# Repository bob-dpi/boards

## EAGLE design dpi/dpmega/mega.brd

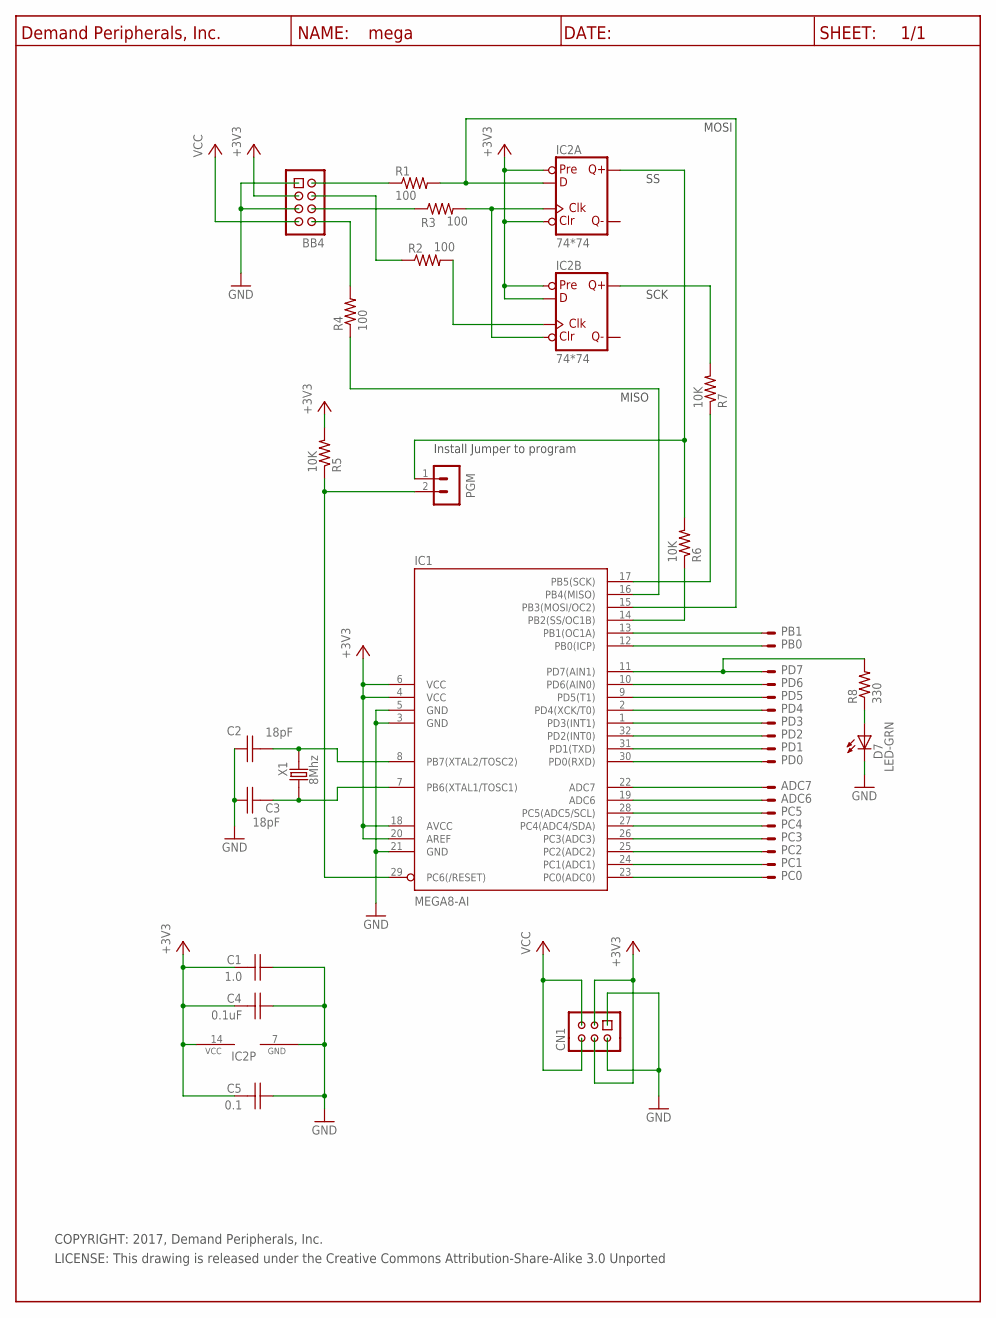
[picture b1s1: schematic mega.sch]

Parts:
ADC6, ADC7: PinHdr254-1(Option); PAD1
BB4: BB4_CON; HDR-4X2
C1: 1.0; C0603
C2, C3: 18pF; C0603
C4: 0.1uF; C0603
C5: 0.1; C0603
CN1: HDR-3X2
D7: LED-GRN; 0805
IC1: MEGA8-AI; TQFP32-08
IC2: 74*74; TSSOP14
PB0, PB1: PinHdr254-1(Option); PAD1
PC0, PC1, PC2, PC3, PC4, PC5: PinHdr254-1(Option); PAD1
PD0, PD1, PD2, PD3, PD4, PD5, PD6, PD7: PinHdr254-1(Option); PAD1
PGM: PinHdr254-2; HDR-2X1
R1, R2, R3, R4: 100; R0603
R5, R6, R7: 10K; R0603
R8: 330; R0603
U$1: DP_FRAME_P; P_FRAME
X1: 8Mhz; NX5032

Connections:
+3V3: BB4.3, C1.2, C4.2, C5.2, CN1.3, CN1.4, IC1.4 (VCC), IC1.6 (VCC), IC1.18 (AVCC), IC1.20 (AREF), IC2.1 (CLR), IC2.4 (PRE), IC2.10 (PRE), IC2.12 (D), IC2.14 (VCC), R5.2
GND: BB4.1, BB4.5, C1.1, C2.1, C3.1, C4.1, C5.1, CN1.1, CN1.2, D7.C, IC1.3 (GND), IC1.5 (GND), IC1.21 (GND), IC2.7 (GND)
unnamed: IC1.29 (PC6(/RESET)), PGM.2 (1), R5.1
unnamed: D7.A, R8.1
unnamed: C3.2, IC1.7 (PB6(XTAL1/TOSC1)), X1.2
unnamed: C2.2, IC1.8 (PB7(XTAL2/TOSC2)), X1.1
unnamed: IC1.23 (PC0(ADC0)), PC0.1
unnamed: IC1.26 (PC3(ADC3)), PC3.1
unnamed: IC1.24 (PC1(ADC1)), PC1.1
unnamed: IC1.25 (PC2(ADC2)), PC2.1
unnamed: IC1.27 (PC4(ADC4/SDA)), PC4.1
unnamed: IC1.28 (PC5(ADC5/SCL)), PC5.1
unnamed: ADC6.1, IC1.19 (ADC6)
unnamed: ADC7.1, IC1.22 (ADC7)
unnamed: IC1.30 (PD0(RXD)), PD0.1
unnamed: IC1.31 (PD1(TXD)), PD1.1
unnamed: IC1.32 (PD2(INT0)), PD2.1
unnamed: IC1.1 (PD3(INT1)), PD3.1
unnamed: IC1.2 (PD4(XCK/T0)), PD4.1
unnamed: IC1.9 (PD5(T1)), PD5.1
unnamed: IC1.10 (PD6(AIN0)), PD6.1
unnamed: IC1.11 (PD7(AIN1)), PD7.1, R8.2
unnamed: IC1.12 (PB0(ICP)), PB0.1
unnamed: IC1.13 (PB1(OC1A)), PB1.1
unnamed: BB4.2, R1.1
unnamed: IC1.15 (PB3(MOSI/OC2)), IC2.2 (D), R1.2
unnamed: BB4.4, R2.1
unnamed: IC2.11 (CLK), R2.2
unnamed: IC2.3 (CLK), IC2.13 (CLR), R3.2
unnamed: BB4.6, R3.1
unnamed: IC2.9 (Q), R7.2
unnamed: IC2.5 (Q), PGM.1 (2), R6.2
unnamed: IC1.16 (PB4(MISO)), R4.1
unnamed: BB4.8, R4.2
unnamed: IC1.14 (PB2(SS/OC1B)), R6.1
unnamed: IC1.17 (PB5(SCK)), R7.1
VCC: BB4.7, CN1.5, CN1.6

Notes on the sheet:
MOSI
MISO
SCK
Install Jumper to program
COPYRIGHT: 2017, Demand Peripherals, Inc.
LICENSE: This drawing is released under the Creative Commons Attribution-Share-Alike 3.0 Unported

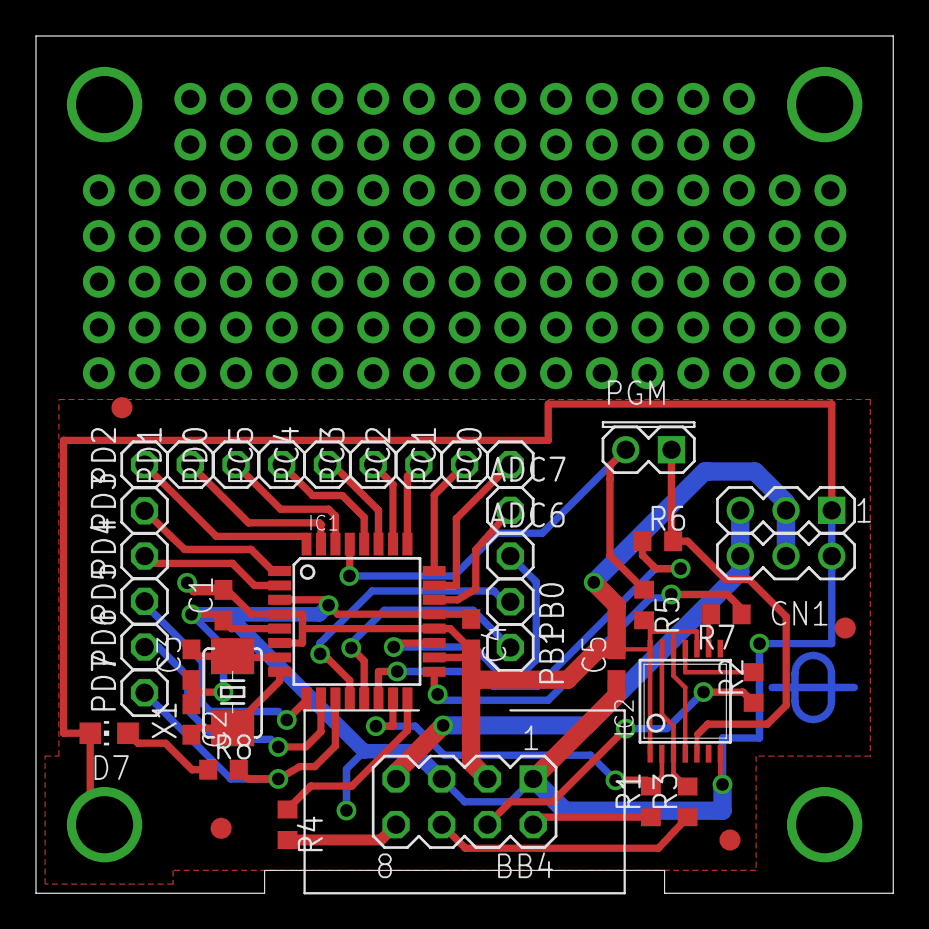
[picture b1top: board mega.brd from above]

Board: 2 copper layers, 47.6 x 47.6 mm, 44 parts (1 on the bottom side), 37 nets.

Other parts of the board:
U$2: DPI-1
U$4, U$5, U$6, U$7: FIDUCIAL

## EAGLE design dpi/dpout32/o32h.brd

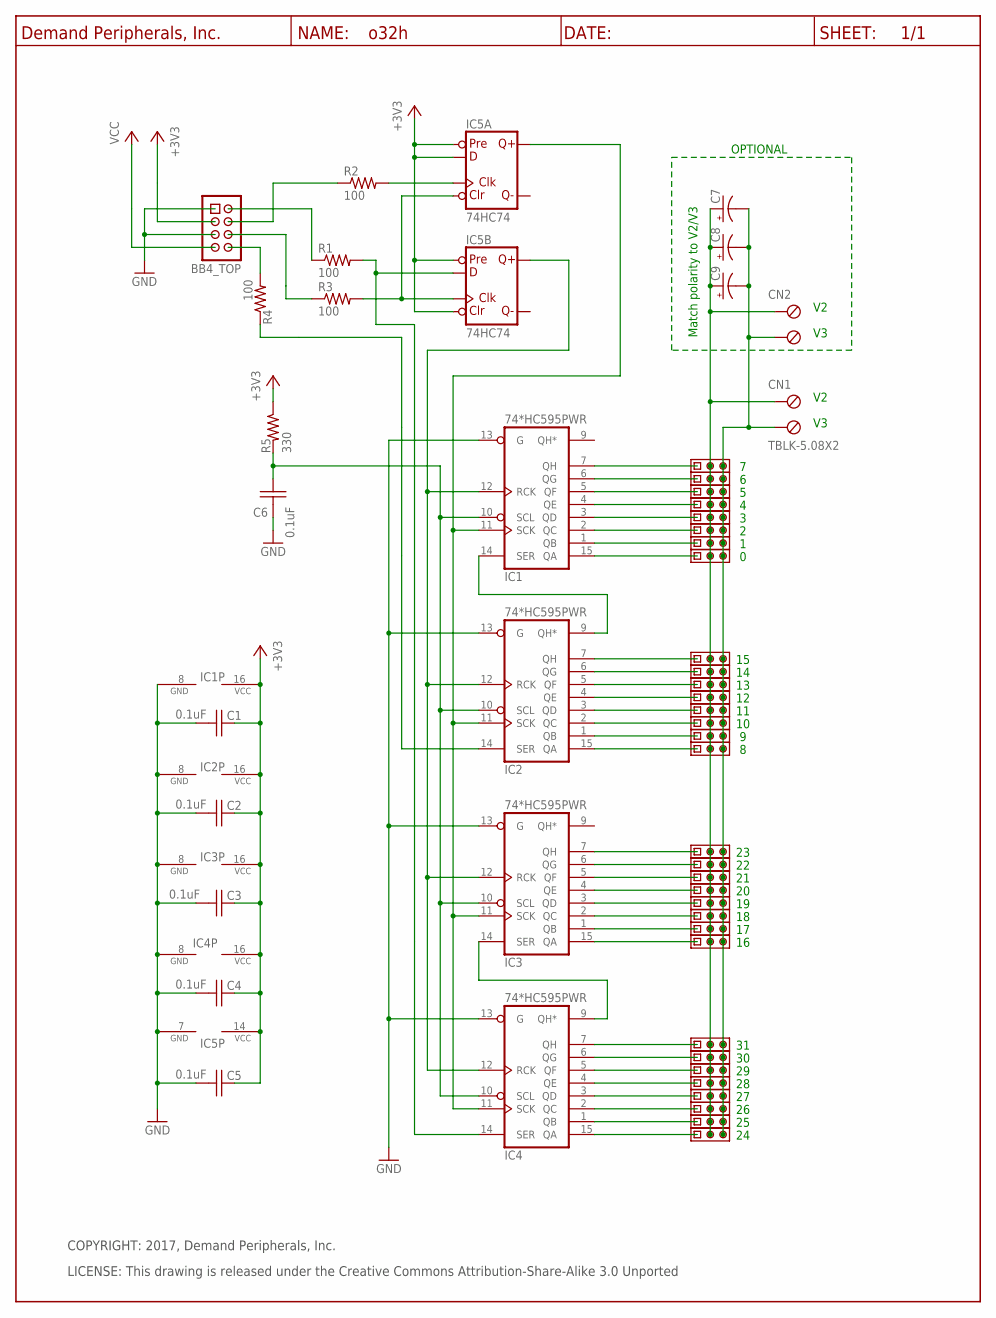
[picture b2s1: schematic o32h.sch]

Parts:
BB4_TOP: Keyed_Pin_Header_4x2(0.1"x0.1"); HDR-4X2
C1, C2, C3, C4, C5, C6: 0.1uF; C0603
C7, C8, C9: OPTIONAL; E7,5-16
CN1, CN2: TBLK-5.08X2; TBLK-5.08-X2
IC1, IC2, IC3, IC4: 74*HC595PWR; SO16
IC5: 74HC74; SO14
R1, R2, R3, R4: 100; R0603
R5: 330; R0603
U$2: DP_FRAME_P; P_FRAME
U$8, U$9, U$10, U$11, U$12, U$13, U$14, U$15, U$16, U$17, U$18, U$19, U$20, U$21, U$22, U$23, U$24, U$25, U$26, U$27, U$28, U$29, U$30, U$31, U$32, U$33, U$34, U$35, U$36, U$37, U$38, U$39: HDR-3X1

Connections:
+3V3: BB4_TOP.3, C1.1, C2.1, C3.1, C4.1, C5.1, IC1.16 (VCC), IC2.16 (VCC), IC3.16 (VCC), IC4.16 (VCC), IC5.2 (D), IC5.4 (PRE), IC5.10 (PRE), IC5.13 (CLR), IC5.14 (VCC), R5.1
GND: BB4_TOP.1, BB4_TOP.5, C1.2, C2.2, C3.2, C4.2, C5.2, C6.2, IC1.8 (GND), IC1.13 (G), IC2.8 (GND), IC2.13 (G), IC3.8 (GND), IC3.13 (G), IC4.8 (GND), IC4.13 (G), IC5.7 (GND)
unnamed: BB4_TOP.8, R4.2
unnamed: IC1.7 (QH), U$8.1
unnamed: IC1.12 (RCK), IC2.12 (RCK), IC3.12 (RCK), IC4.12 (RCK), IC5.9 (Q)
unnamed: IC1.11 (SCK), IC2.11 (SCK), IC3.11 (SCK), IC4.11 (SCK), IC5.5 (Q)
unnamed: IC1.6 (QG), U$9.1
unnamed: IC1.5 (QF), U$10.1
unnamed: IC1.4 (QE), U$11.1
unnamed: IC1.3 (QD), U$12.1
unnamed: IC1.2 (QC), U$13.1
unnamed: IC1.1 (QB), U$14.1
unnamed: IC1.15 (QA), U$15.1
unnamed: IC2.7 (QH), U$16.1
unnamed: IC2.6 (QG), U$17.1
unnamed: IC2.5 (QF), U$18.1
unnamed: IC2.4 (QE), U$19.1
unnamed: IC2.3 (QD), U$20.1
unnamed: IC2.2 (QC), U$21.1
unnamed: IC2.1 (QB), U$22.1
unnamed: IC2.15 (QA), U$23.1
unnamed: IC3.7 (QH), U$24.1
unnamed: IC3.6 (QG), U$25.1
unnamed: IC3.5 (QF), U$26.1
unnamed: IC3.4 (QE), U$27.1
unnamed: IC3.3 (QD), U$28.1
unnamed: IC3.2 (QC), U$29.1
unnamed: BB4_TOP.2, R1.1
unnamed: IC3.1 (QB), U$30.1
unnamed: IC5.3 (CLK), R2.2
unnamed: IC4.14 (SER), IC5.12 (D), R1.2
unnamed: IC5.1 (CLR), IC5.11 (CLK), R3.2
unnamed: IC2.14 (SER), R4.1
unnamed: BB4_TOP.6, R3.1
unnamed: IC3.14 (SER), IC4.9 (QH*)
unnamed: BB4_TOP.4, R2.1
unnamed: IC3.15 (QA), U$31.1
unnamed: C6.1, IC1.10 (SCL), IC2.10 (SCL), IC3.10 (SCL), IC4.10 (SCL), R5.2
unnamed: IC4.7 (QH), U$32.1
unnamed: IC4.6 (QG), U$33.1
unnamed: IC4.5 (QF), U$34.1
unnamed: IC4.4 (QE), U$35.1
unnamed: IC4.3 (QD), U$36.1
unnamed: IC4.2 (QC), U$37.1
unnamed: IC4.1 (QB), U$38.1
unnamed: IC4.15 (QA), U$39.1
unnamed: IC1.14 (SER), IC2.9 (QH*)
V2: C7.+, C8.+, C9.+, CN1.1 (KL), CN2.1 (KL), U$8.2, U$9.2, U$10.2, U$11.2, U$12.2, U$13.2, U$14.2, U$15.2, U$16.2, U$17.2, U$18.2, U$19.2, U$20.2, U$21.2, U$22.2, U$23.2, U$24.2, U$25.2, U$26.2, U$27.2, U$28.2, U$29.2, U$30.2, U$31.2, U$32.2, U$33.2, U$34.2, U$35.2, U$36.2, U$37.2, U$38.2, U$39.2
V3: C7.-, C8.-, C9.-, CN1.2 (KL1), CN2.2 (KL1), U$8.3, U$9.3, U$10.3, U$11.3, U$12.3, U$13.3, U$14.3, U$15.3, U$16.3, U$17.3, U$18.3, U$19.3, U$20.3, U$21.3, U$22.3, U$23.3, U$24.3, U$25.3, U$26.3, U$27.3, U$28.3, U$29.3, U$30.3, U$31.3, U$32.3, U$33.3, U$34.3, U$35.3, U$36.3, U$37.3, U$38.3, U$39.3
VCC: BB4_TOP.7

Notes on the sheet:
COPYRIGHT: 2017, Demand Peripherals, Inc.
LICENSE: This drawing is released under the Creative Commons Attribution-Share-Alike 3.0 Unported
OPTIONAL
Match polarity to V2/V3

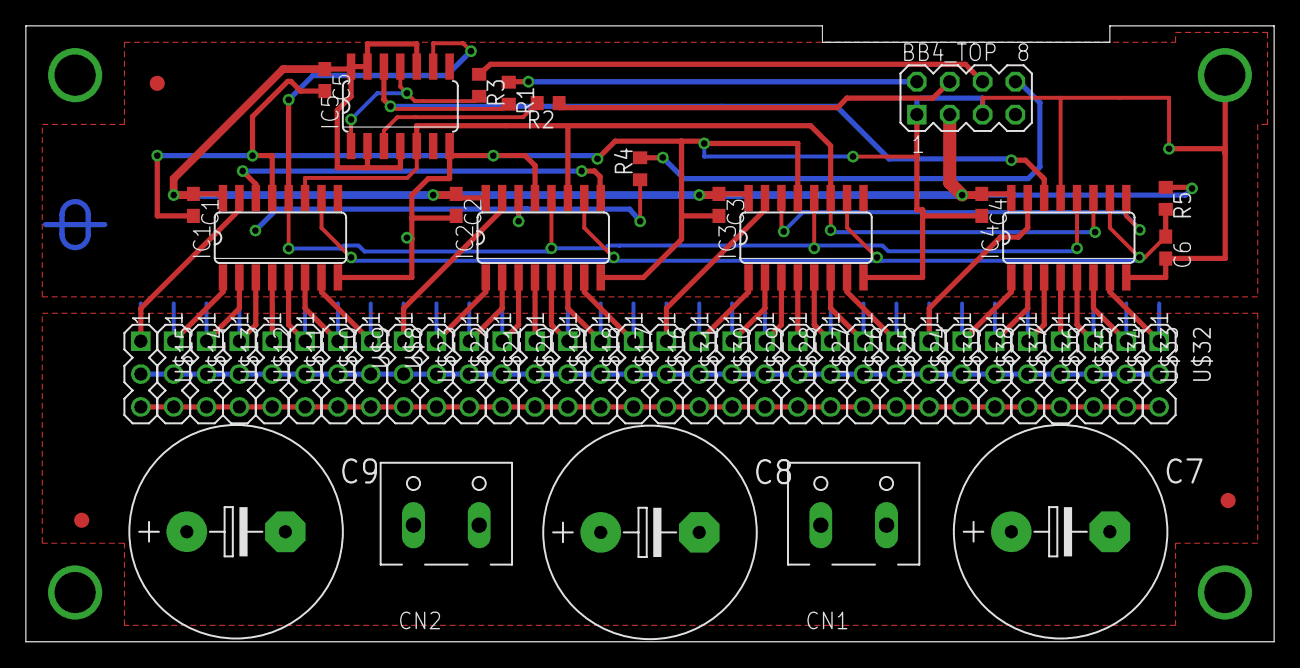
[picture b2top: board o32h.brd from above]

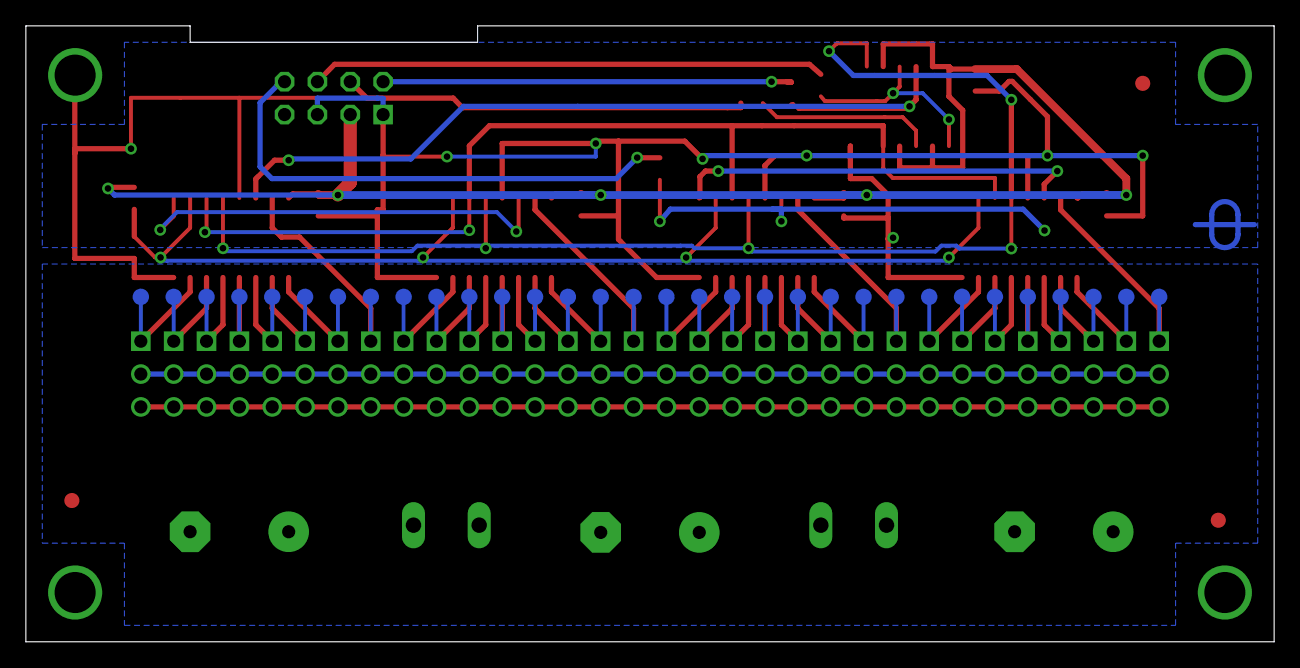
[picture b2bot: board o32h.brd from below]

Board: 2 copper layers, 96.5 x 47.6 mm, 93 parts (33 on the bottom side), 49 nets.

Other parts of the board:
E$1, E$2, E$3, E$4, E$5, E$7, E$8, E$9, E$10, E$11, E$12, E$13, E$14, E$15, E$16, E$17, E$18, E$19, E$20, E$21, E$22, E$23, E$24, E$26, E$27, E$28, E$29, E$30, E$31, E$32, E$33, E$34: TEST-POINT
E$25: P_FRAME
U$1: P_FRAME
U$4, U$5, U$6: FIDUCIAL
U$7: DPI-1

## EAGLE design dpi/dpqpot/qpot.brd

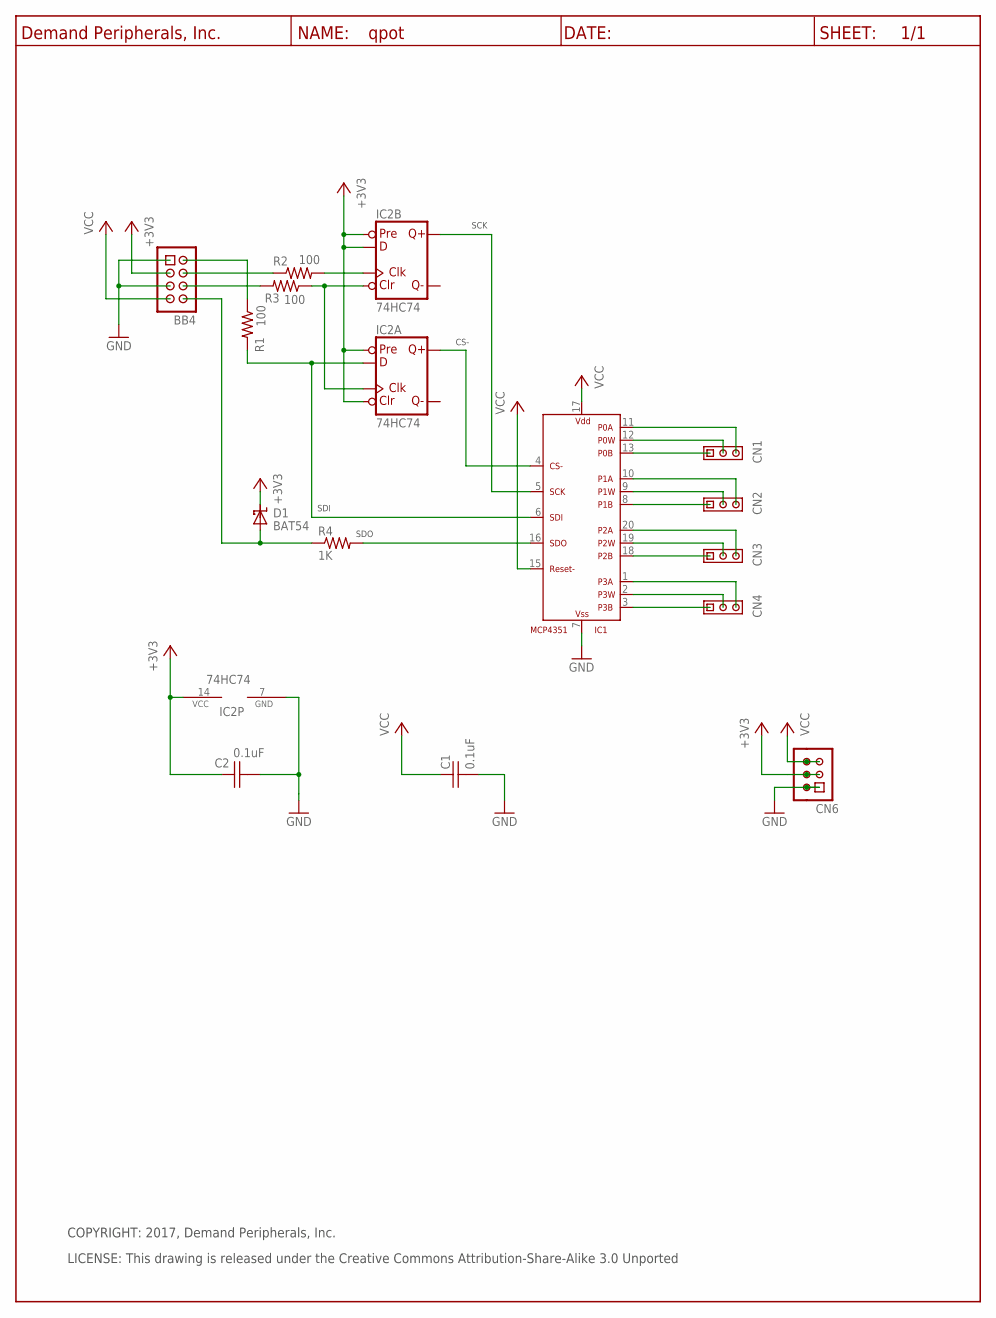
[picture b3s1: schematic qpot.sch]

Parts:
BB4: BB_CON; HDR-4X2
C1, C2: 0.1uF; C0603
CN1, CN2, CN3, CN4: HDR-3X1
CN6: HDR-3X2
D1: BAT54; SOT23
IC1: MCP4351; TSSOP20
IC2: 74HC74; SO14
R1, R2, R3: 100; R0603
R4: 1K; R0603
U$3: DP_FRAME_P; P_FRAME

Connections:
+3V3: BB4.3, C2.1, CN6.3, CN6.4, D1.3 (CC), IC2.1 (CLR), IC2.4 (PRE), IC2.10 (PRE), IC2.12 (D), IC2.14 (VCC)
GND: BB4.1, BB4.5, C1.2, C2.2, CN6.1, CN6.2, IC1.7 (VSS), IC2.7 (GND)
unnamed: CN1.1, IC1.13 (P0B)
unnamed: CN1.2, IC1.12 (P0W)
unnamed: CN1.3, IC1.11 (P0A)
unnamed: CN2.1, IC1.8 (P1B)
unnamed: CN2.2, IC1.9 (P1W)
unnamed: CN2.3, IC1.10 (P1A)
unnamed: BB4.8, D1.1 (A), R4.1
unnamed: IC1.16 (SDO), R4.2
unnamed: IC2.3 (CLK), IC2.13 (CLR), R3.1
unnamed: BB4.4, R2.1
unnamed: IC1.6 (SDI), IC2.2 (D), R1.2
unnamed: IC2.11 (CLK), R2.2
unnamed: CN3.1, IC1.18 (P2B)
unnamed: CN3.2, IC1.19 (P2W)
unnamed: BB4.6, R3.2
unnamed: BB4.2, R1.1
unnamed: CN3.3, IC1.20 (P2A)
unnamed: CN4.1, IC1.3 (P3B)
unnamed: IC1.4 (CS-), IC2.5 (Q)
unnamed: IC1.5 (SCK), IC2.9 (Q)
unnamed: CN4.2, IC1.2 (P3W)
unnamed: CN4.3, IC1.1 (P3A)
VCC: BB4.7, C1.1, CN6.5, CN6.6, IC1.15 (RESET-), IC1.17 (VDD)

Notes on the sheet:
SCK
CS-
SDI
LICENSE: This drawing is released under the Creative Commons Attribution-Share-Alike 3.0 Unported
COPYRIGHT: 2017, Demand Peripherals, Inc.
SDO

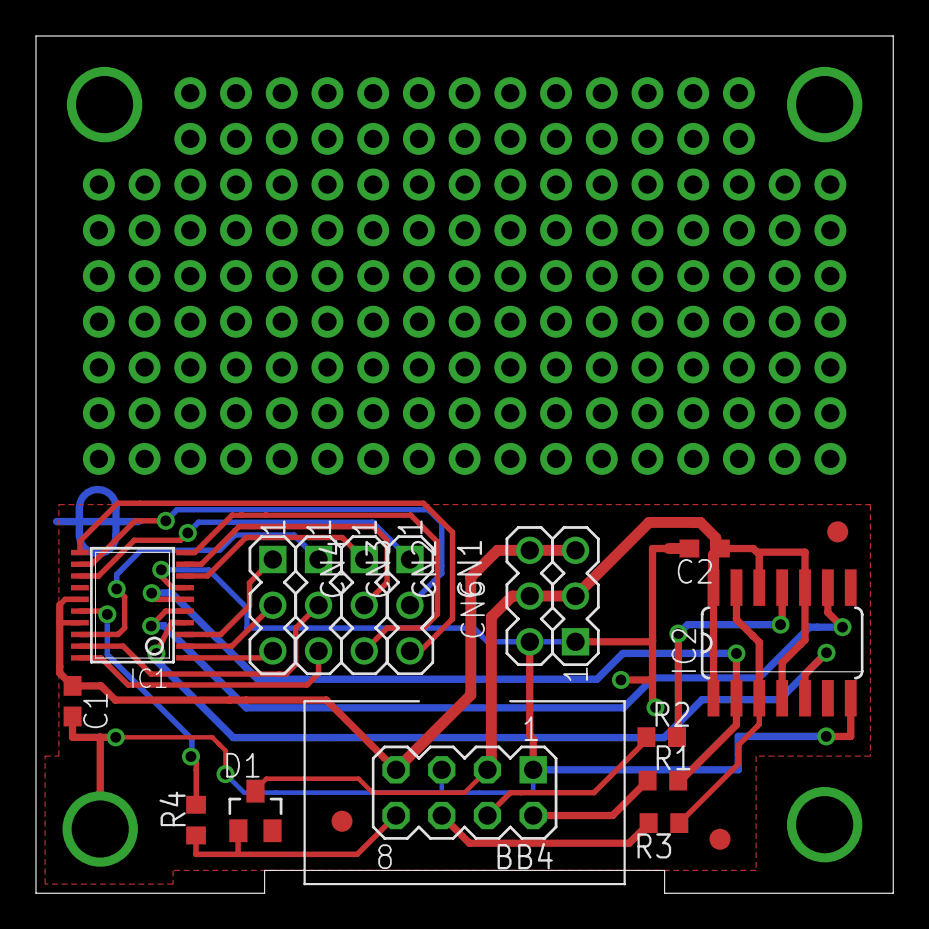
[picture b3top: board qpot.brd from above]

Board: 2 copper layers, 47.6 x 47.6 mm, 20 parts (1 on the bottom side), 25 nets.

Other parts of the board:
U$1: DPI-1
U$4, U$5, U$6: FIDUCIAL

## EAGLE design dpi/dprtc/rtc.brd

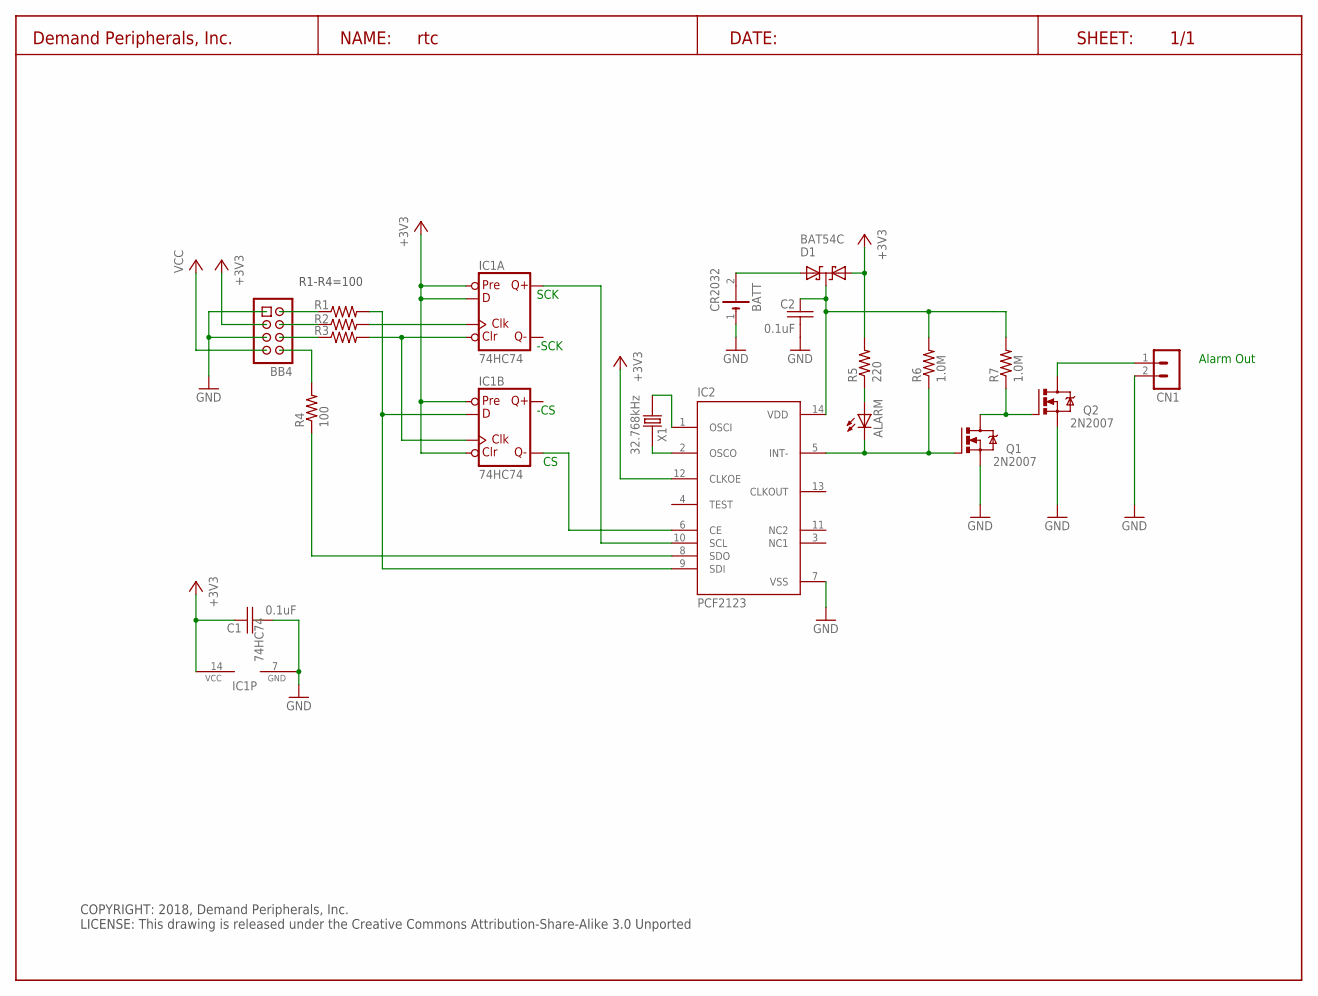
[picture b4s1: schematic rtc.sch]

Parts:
ALARM: Red_LED; 0805
BATT: CR2032; CR2032_KEYSTONE
BB4: BB_CON; HDR-4X2
C1, C2: 0.1uF; C0603
CN1: HDR-2X1-LCK; HDR-2X1
D1: BAT54C; SOT23
IC1: 74HC74; SO14
IC2: PCF2123; TSSOP14
Q1, Q2: 2N2007; SOT23
R1, R2, R3, R4: 100; R0603
R5: 220; R0603
R6, R7: 1.0M; R0603
U$1: DP_FRAME_L; LETTER_L
X1: 32.768kHz; 4-SOJ

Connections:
+3V3: BB4.3, C1.1, D1.2 (A), IC1.2 (D), IC1.4 (PRE), IC1.10 (PRE), IC1.13 (CLR), IC1.14 (VCC), IC2.12 (CLKOE), R5.2
GND: BATT.1 (-), BB4.1, BB4.5, C1.2, C2.2, CN1.2 (1), IC1.7 (GND), IC2.7 (VSS), Q1.3 (S), Q2.3 (S)
unnamed: BB4.4, R2.1
unnamed: BB4.6, R3.1
unnamed: IC1.3 (CLK), R2.2
unnamed: IC1.1 (CLR), IC1.11 (CLK), R3.2
unnamed: ALARM.A, R5.1
unnamed: Q1.2 (D), Q2.1 (G), R7.1
unnamed: C2.1, D1.3 (CC), IC2.14 (VDD), R6.2, R7.2
unnamed: IC2.2 (OSCO), X1.4 (2)
unnamed: IC2.1 (OSCI), X1.1
unnamed: BATT.2 (+), D1.1 (A1)
unnamed: BB4.2, R1.1
unnamed: ALARM.C, IC2.5 (INT-), Q1.1 (G), R6.1
unnamed: IC1.12 (D), IC2.9 (SDI), R1.2
unnamed: BB4.8, R4.2
unnamed: CN1.1 (2), Q2.2 (D)
unnamed: IC2.8 (SDO), R4.1
unnamed: IC1.8 (!Q), IC2.6 (CE)
unnamed: IC1.5 (Q), IC2.10 (SCL)
VCC: BB4.7

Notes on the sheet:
Alarm Out
SCK
-SCK
-CS
R1-R4=100
COPYRIGHT: 2018, Demand Peripherals, Inc. LICENSE: This drawing is released under the Creative Commons Attribution-Share-Alike 3.0 Unported

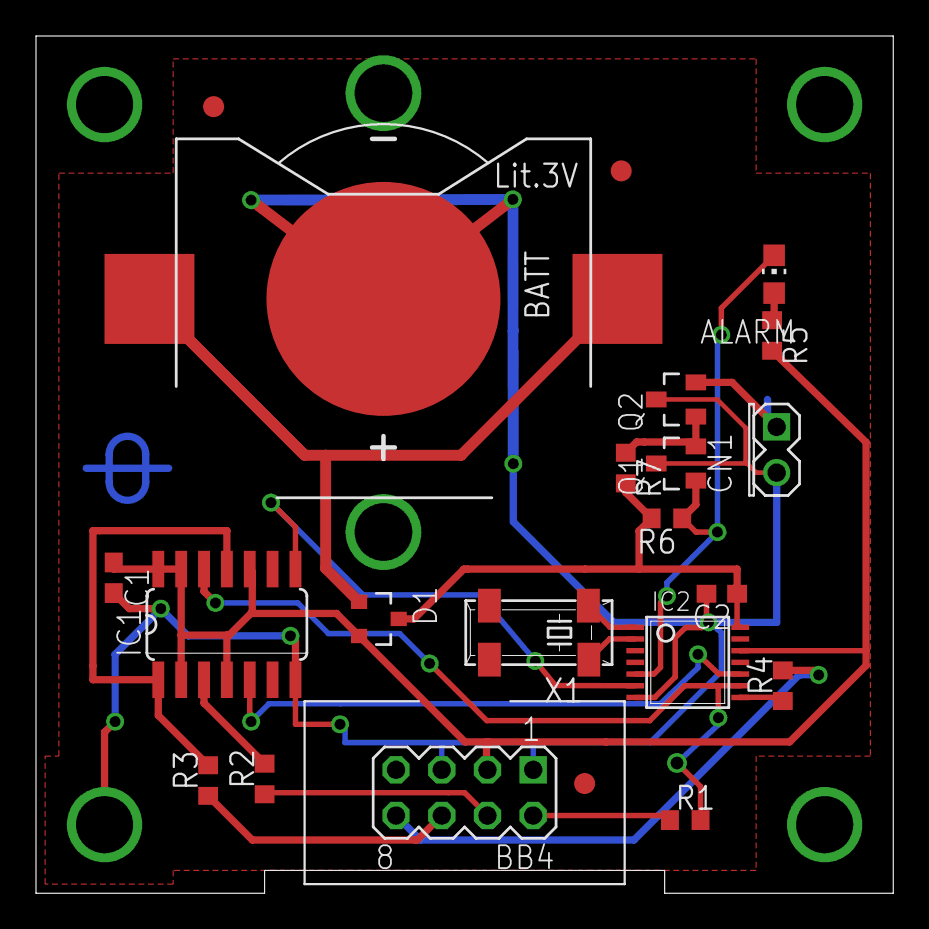
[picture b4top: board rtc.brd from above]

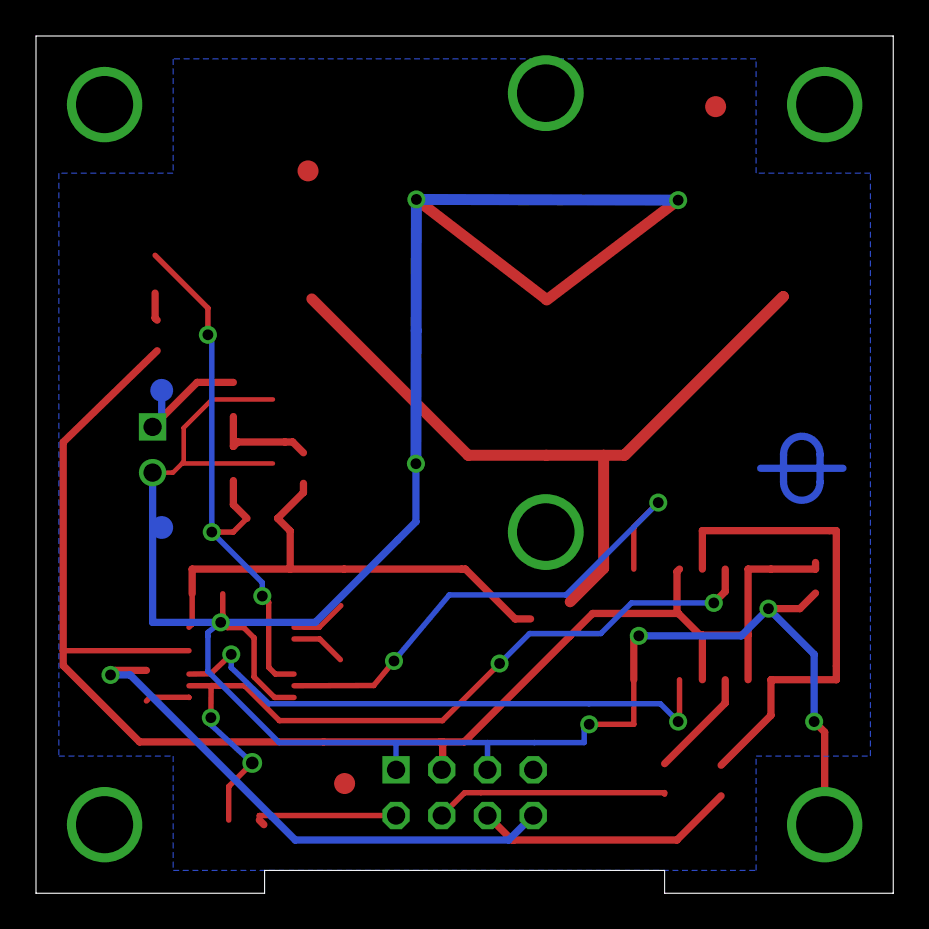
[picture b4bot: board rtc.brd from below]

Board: 2 copper layers, 47.6 x 47.6 mm, 26 parts (3 on the bottom side), 20 nets.

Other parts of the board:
E$1, E$2: TEST-POINT
U$2: DPI-1
U$3, U$4, U$5: FIDUCIAL

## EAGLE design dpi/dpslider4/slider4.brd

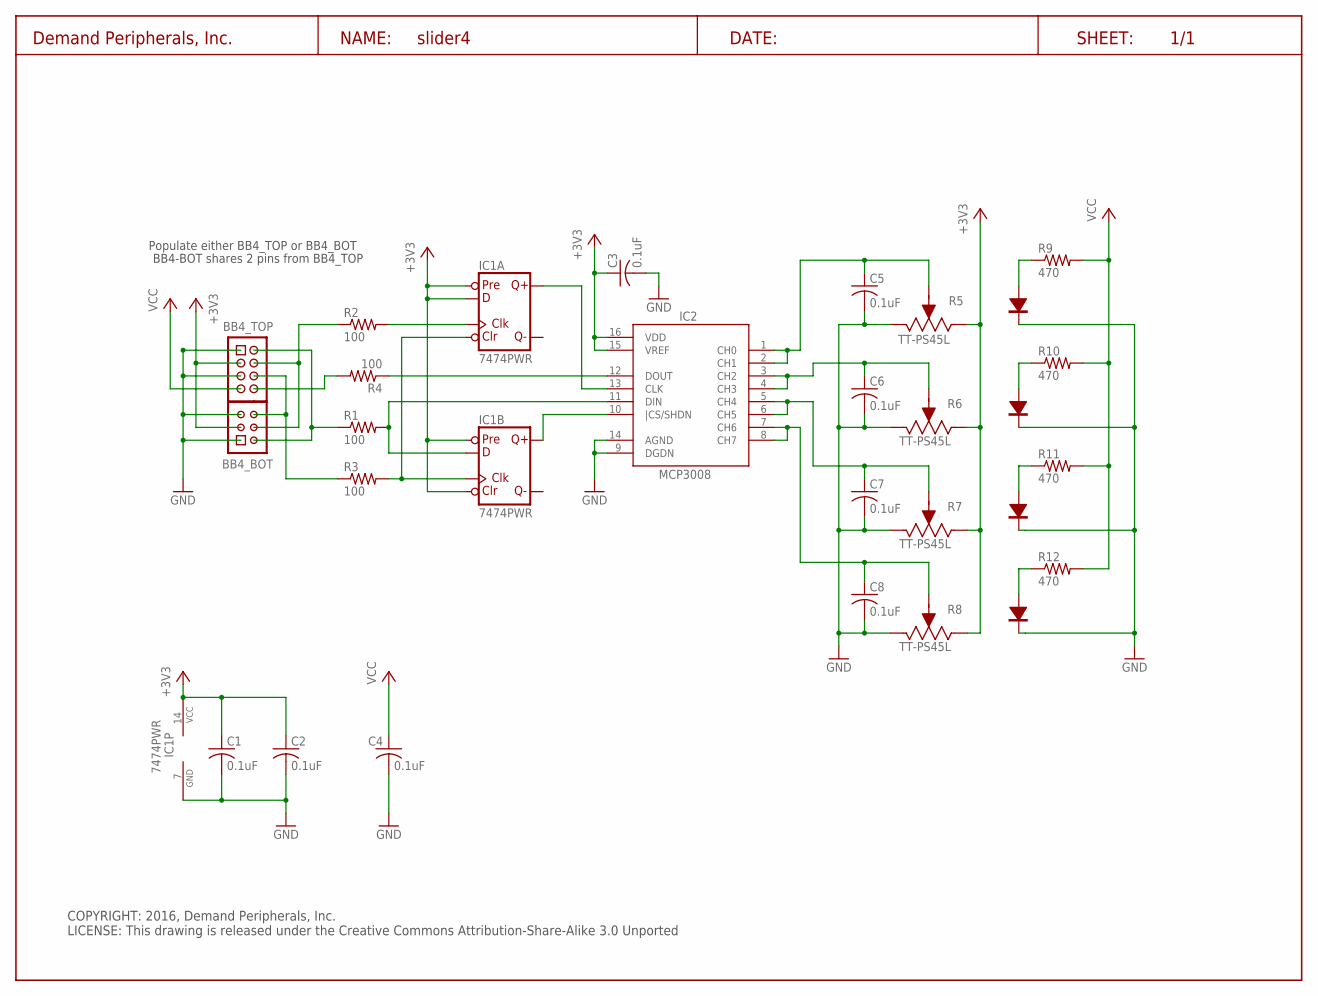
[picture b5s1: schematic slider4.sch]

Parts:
BB4_BOT: Hdr3x2; HDR-3X2
BB4_TOP: Hdr4x2; HDR-4X2
C1, C2, C3, C4, C5, C6, C7, C8: 0.1uF; C0603
IC1: 7474PWR; SO14
IC2: MCP3008; SO16
R1, R2, R3, R4: 100; R0603
R5, R6, R7, R8: TT-PS45L
R9, R10, R11, R12: 470; R0603
U$7: DP_FRAME_L; LETTER_L

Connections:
+3V3: BB4_BOT.3, BB4_TOP.3, C1.1, C2.1, C3.1, IC1.2 (D), IC1.4 (PRE), IC1.10 (PRE), IC1.13 (CLR), IC1.14 (VCC), IC2.15 (VREF), IC2.16 (VDD), R5.P$2 (2), R6.P$2 (2), R7.P$2 (2), R8.P$2 (2)
GND: BB4_BOT.1, BB4_BOT.5, BB4_TOP.1, BB4_TOP.5, C1.2, C2.2, C3.2, C4.2, C5.2, C6.2, C7.2, C8.2, IC1.7 (GND), IC2.9 (DGDN), IC2.14 (AGND), R5.P$4 (5), R5.P$6 (6), R6.P$4 (5), R6.P$6 (6), R7.P$4 (5), R7.P$6 (6), R8.P$4 (5), R8.P$6 (6)
unnamed: BB4_BOT.2, BB4_TOP.2, R1.1
unnamed: IC1.9 (Q), IC2.10 (|CS/SHDN)
unnamed: IC1.5 (Q), IC2.13 (CLK)
unnamed: IC2.12 (DOUT), R4.1
unnamed: BB4_BOT.4, BB4_TOP.4, R2.1
unnamed: R5.P$5 (4), R9.1
unnamed: R6.P$5 (4), R10.1
unnamed: R7.P$5 (4), R11.1
unnamed: R8.P$5 (4), R12.1
unnamed: BB4_BOT.6, BB4_TOP.6, R3.1
unnamed: C5.1, IC2.1 (CH0), IC2.2 (CH1), R5.P$1 (1)
unnamed: C6.1, IC2.3 (CH2), IC2.4 (CH3), R6.P$1 (1)
unnamed: C7.1, IC2.5 (CH4), IC2.6 (CH5), R7.P$1 (1)
unnamed: BB4_TOP.8, R4.2
unnamed: C8.1, IC2.7 (CH6), IC2.8 (CH7), R8.P$1 (1)
unnamed: IC1.3 (CLK), R2.2
unnamed: IC1.12 (D), IC2.11 (DIN), R1.2
unnamed: IC1.1 (CLR), IC1.11 (CLK), R3.2
VCC: BB4_TOP.7, C4.1, R9.2, R10.2, R11.2, R12.2

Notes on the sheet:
Populate either BB4_TOP or BB4_BOT
BB4-BOT shares 2 pins from BB4_TOP
COPYRIGHT: 2016, Demand Peripherals, Inc. LICENSE: This drawing is released under the Creative Commons Attribution-Share-Alike 3.0 Unported

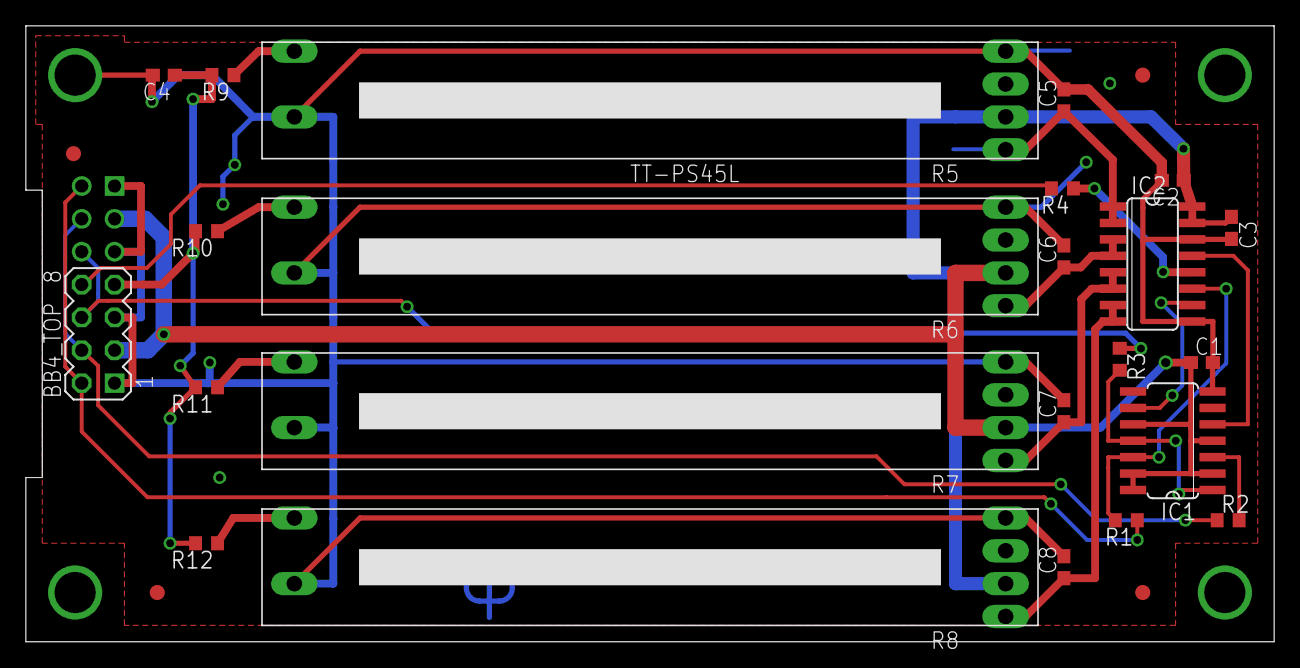
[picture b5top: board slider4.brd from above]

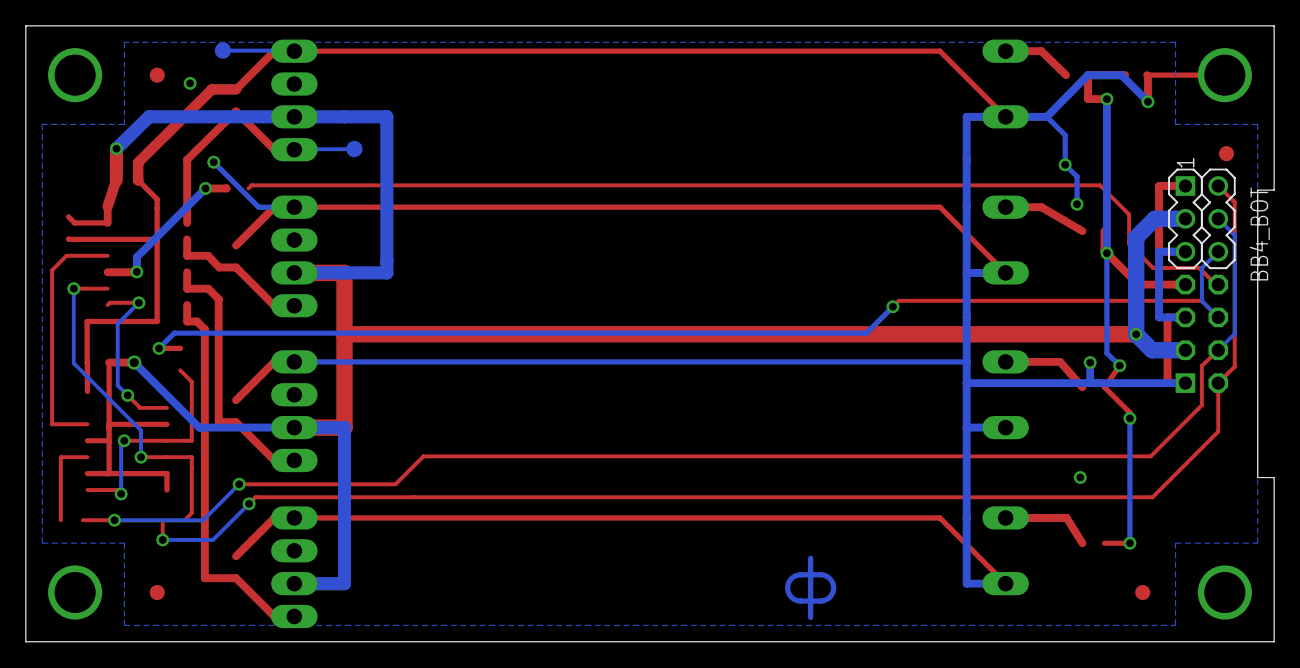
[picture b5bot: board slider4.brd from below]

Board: 2 copper layers, 96.5 x 47.6 mm, 32 parts (4 on the bottom side), 21 nets.

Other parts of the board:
E$1, E$2: TEST-POINT
U$1: DPI-1
U$3, U$4, U$5, U$6: FIDUCIAL

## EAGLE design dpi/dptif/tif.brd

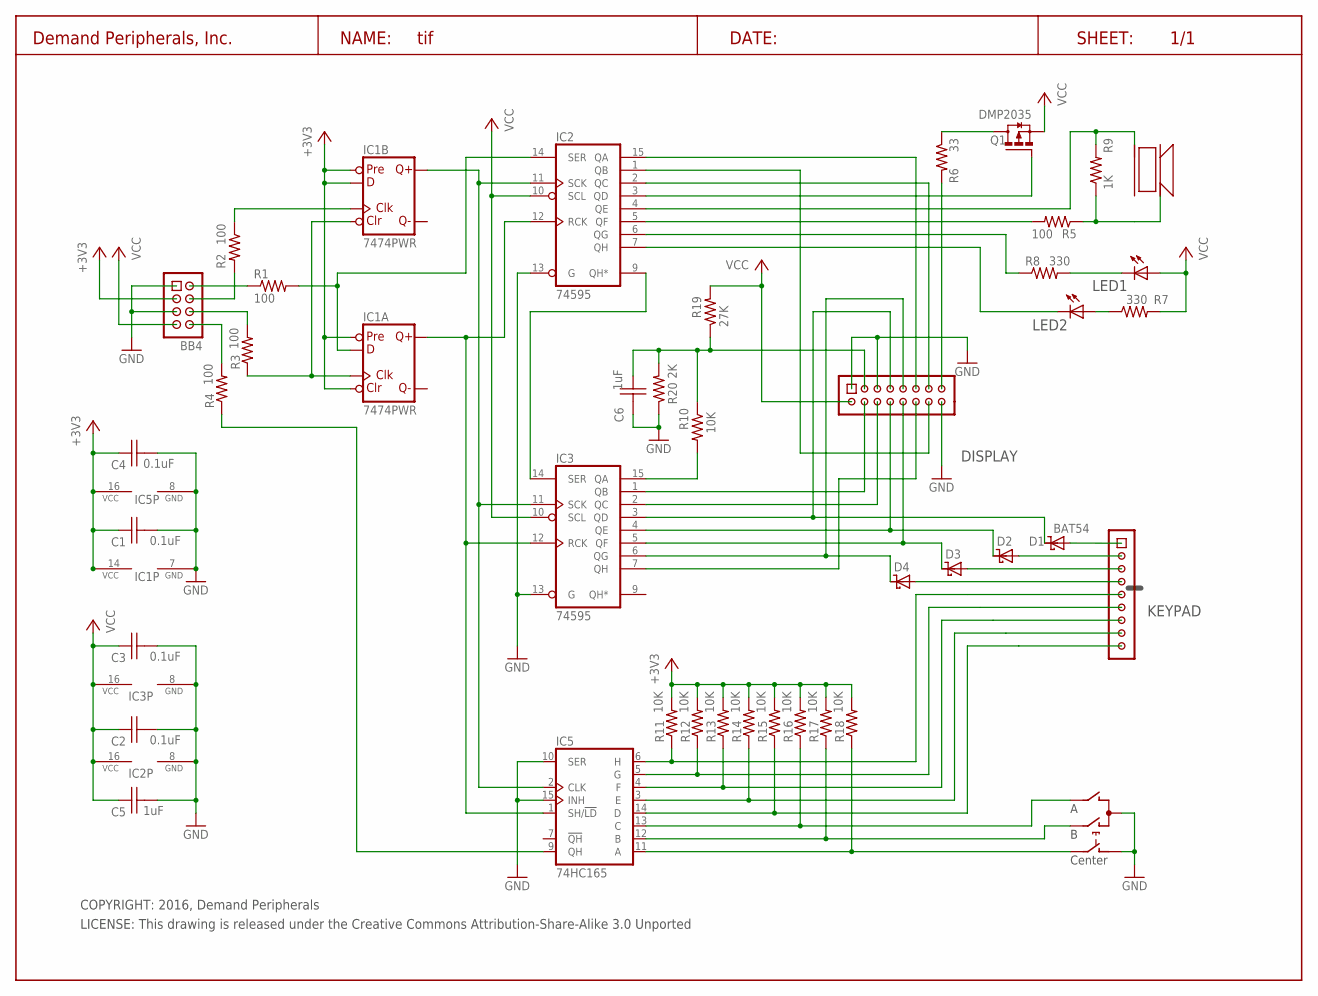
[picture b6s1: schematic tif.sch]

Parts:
2: ROTARY_ENCODER_W_SWITCHCTS_V_290; CTS_290_VERT
BB4: Hdr_4x2; HDR-4X2
C1, C2, C3, C4: 0.1uF; C0603
C5, C6: 1uF; C0603
D1, D2, D3, D4: BAT54; SOT23
DISPLAY: HDR-8X2
IC1: 7474PWR; SO14
IC2, IC3: 74595; SO16
IC5: 74HC165; SO16
KEYPAD: HDR-9X1
LED1: LED-0805-GRN; 0805
LED2: LED-0805-RED; 0805
Q1: DMP2035; SOT23
R1, R2, R3, R4, R5: 100; R0603
R6: 33; R0603
R7, R8: 330; R0603
R9: 1K; R0603
R10, R11, R12, R13, R14, R15, R16, R17, R18: 10K; R0603
R19: 27K; R0603
R20: 2K; R0603
SPK1: PKM13EPY
U$5: DP_FRAME_L; LETTER_L

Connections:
+3V3: BB4.3, C1.1, C4.1, IC1.1 (CLR), IC1.4 (PRE), IC1.10 (PRE), IC1.12 (D), IC1.14 (VCC), IC5.16 (VCC), R11.2, R12.2, R13.2, R14.2, R15.2, R16.2, R17.2, R18.2
GND: 2.C, 2.D, BB4.1, BB4.5, C1.2, C2.2, C3.2, C4.2, C5.2, C6.2, DISPLAY.1, DISPLAY.5, DISPLAY.16, IC1.7 (GND), IC2.8 (GND), IC2.13 (G), IC3.8 (GND), IC3.13 (G), IC5.8 (GND), IC5.10 (SER), IC5.15 (INH), R20.1
unnamed: BB4.2, R1.1
unnamed: BB4.8, R4.2
unnamed: IC5.9 (QH), R4.1
unnamed: BB4.6, R3.2
unnamed: BB4.4, R2.2
unnamed: IC1.2 (D), IC2.14 (SER), R1.2
unnamed: IC2.9 (QH*), IC3.14 (SER)
unnamed: C6.1, DISPLAY.3, R10.1, R19.1, R20.2
unnamed: 2.E, IC5.11 (A), R18.1
unnamed: D3.3 (CC), DISPLAY.10, IC3.5 (QF)
unnamed: IC3.15 (QA), R10.2
unnamed: IC1.9 (Q), IC2.11 (SCK), IC3.11 (SCK), IC5.2 (CLK)
unnamed: IC1.3 (CLK), IC1.13 (CLR), R3.1
unnamed: IC2.7 (QH), LED2.C
unnamed: IC1.11 (CLK), R2.1
unnamed: IC2.3 (QD), Q1.1 (G)
unnamed: D1.1 (A), KEYPAD.1
unnamed: D2.1 (A), KEYPAD.2
unnamed: D3.1 (A), KEYPAD.3
unnamed: D4.1 (A), KEYPAD.4
unnamed: D1.3 (CC), DISPLAY.7, IC3.3 (QD)
unnamed: IC2.6 (QG), R8.1
unnamed: IC2.5 (QF), R5.2
unnamed: IC2.4 (QE), R9.2, SPK1.1 (GND1)
unnamed: R5.1, R9.1, SPK1.2 (GND2)
unnamed: Q1.3 (D), R6.1
unnamed: DISPLAY.11, IC2.15 (QA)
unnamed: DISPLAY.14, IC2.1 (QB)
unnamed: DISPLAY.13, IC2.2 (QC)
unnamed: LED1.C, R8.2
unnamed: IC1.5 (Q), IC2.12 (RCK), IC3.12 (RCK), IC5.1 (SH/!LD)
unnamed: DISPLAY.4, IC3.1 (QB)
unnamed: D4.3 (CC), DISPLAY.9, IC3.6 (QG)
unnamed: IC5.6 (H), KEYPAD.5, R11.1
unnamed: DISPLAY.6, IC3.2 (QC)
unnamed: IC5.5 (G), KEYPAD.6, R12.1
unnamed: IC5.4 (F), KEYPAD.7, R13.1
unnamed: DISPLAY.15, R6.2
unnamed: LED2.A, R7.1
unnamed: DISPLAY.12, IC3.7 (QH)
unnamed: D2.3 (CC), DISPLAY.8, IC3.4 (QE)
unnamed: IC5.3 (E), KEYPAD.8, R14.1
unnamed: 2.B, IC5.13 (C), R16.1
unnamed: 2.A, IC5.12 (B), R17.1
unnamed: IC5.14 (D), KEYPAD.9, R15.1
VCC: BB4.7, C2.1, C3.1, C5.1, DISPLAY.2, IC2.10 (SCL), IC2.16 (VCC), IC3.10 (SCL), IC3.16 (VCC), LED1.A, Q1.2 (S), R7.2, R19.2

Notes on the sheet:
Center
COPYRIGHT: 2016, Demand Peripherals
LICENSE: This drawing is released under the Creative Commons Attribution-Share-Alike 3.0 Unported

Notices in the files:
dpi/dpmega/mega.brd:
(C) 2017, Demand Peripherals, Inc.
dpi/dpqpot/qpot.brd:
(C) 2018, Demand Peripherals, Inc.
